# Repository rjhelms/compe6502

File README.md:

# compe6502

A very much work-in-progress homebrew 6502 system.

Hardware is currently built off of a 6502 protoboard, available at https://github.com/rjhelms/6502proto.

All hardware CC-BY-SA 4.0. All software zlib license unless otherwise specified.

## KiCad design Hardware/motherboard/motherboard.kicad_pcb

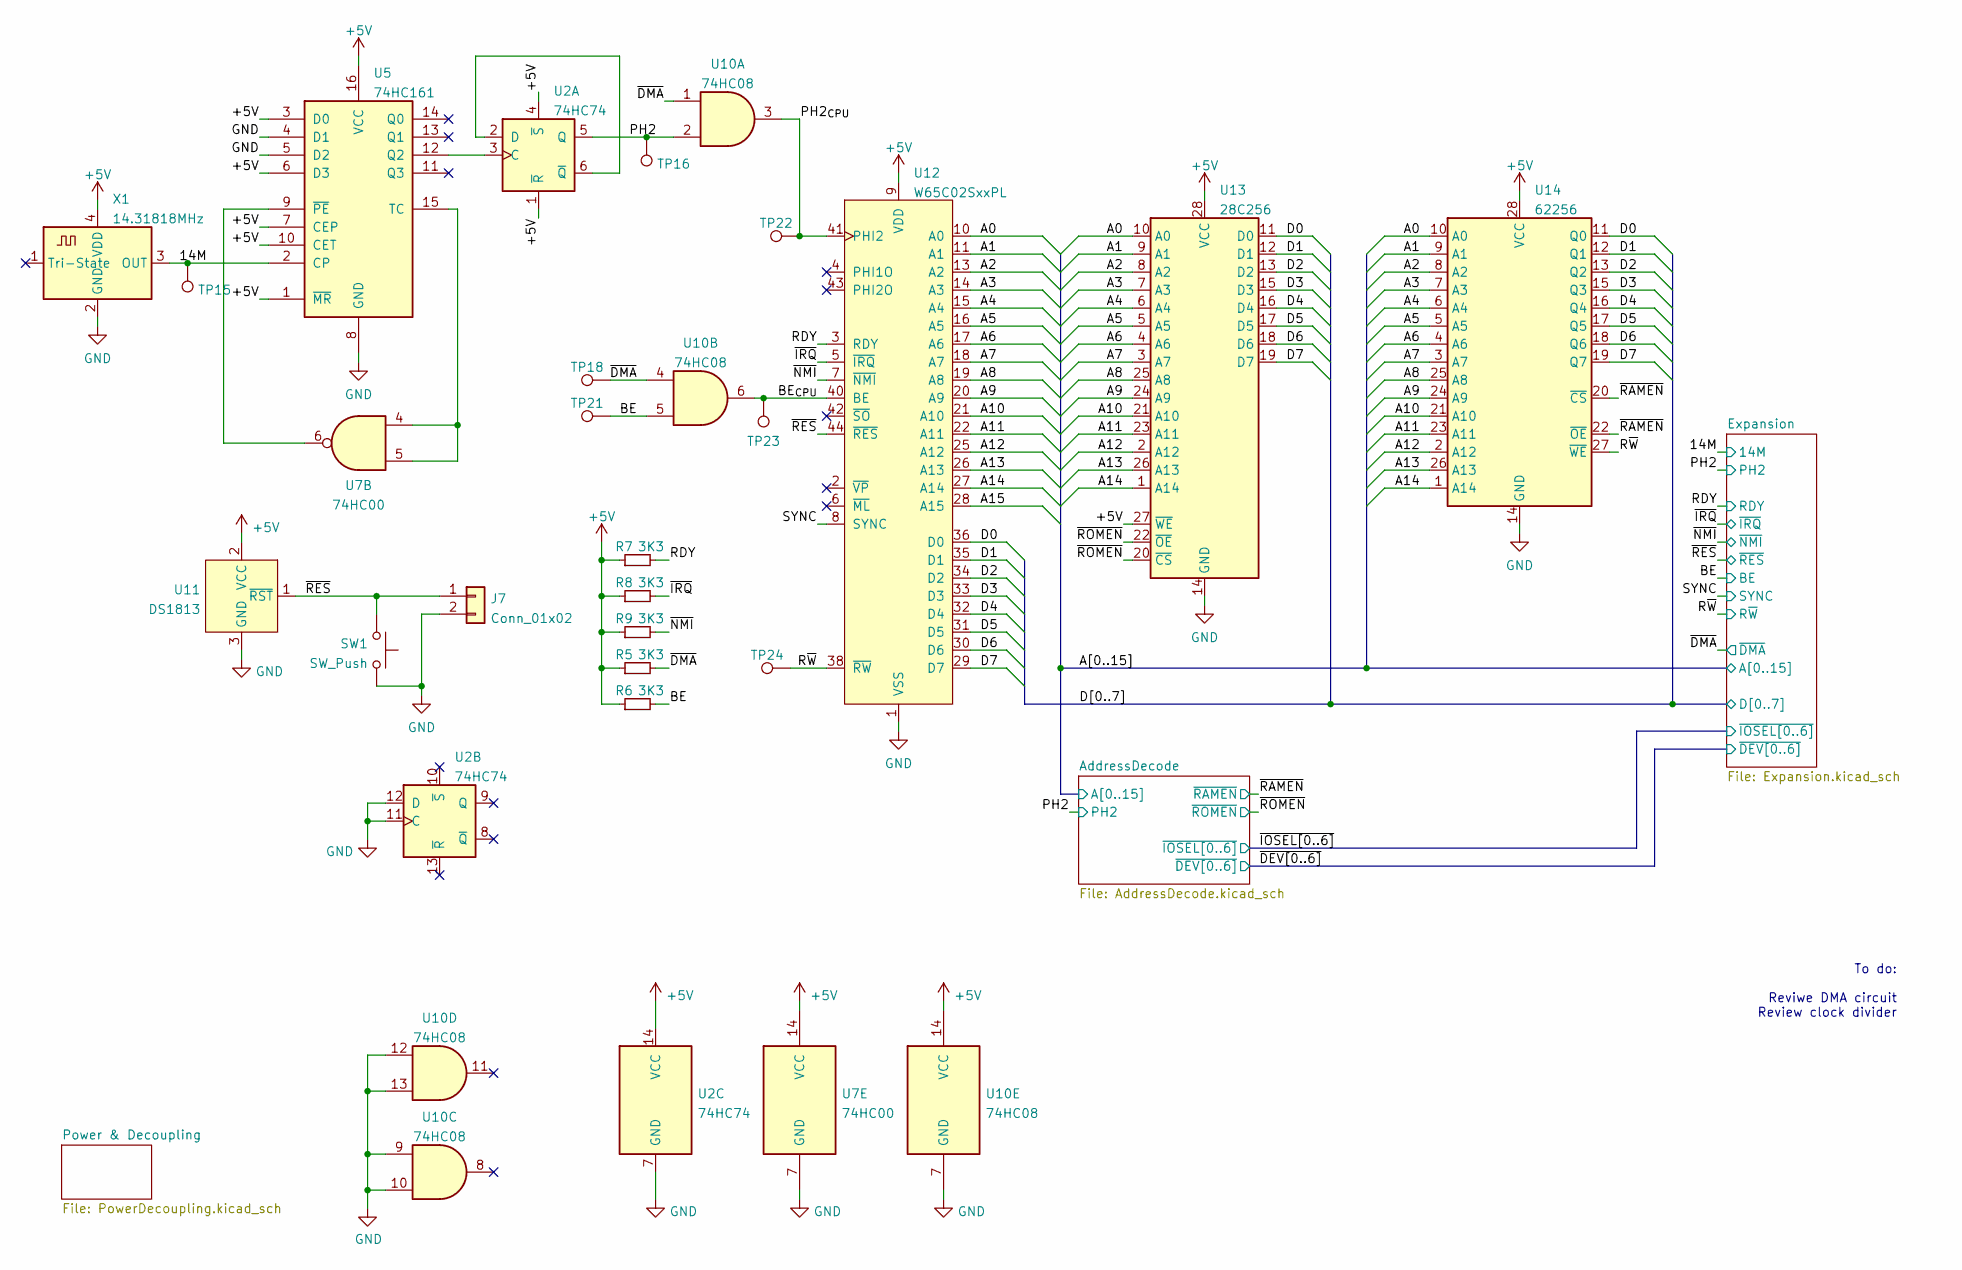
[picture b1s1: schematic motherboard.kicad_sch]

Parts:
J7: Conn_01x02; PinHeader_1x02_P2.54mm_Vertical
R5, R6, R7, R8, R9: 3K3; R_0805_2012Metric
SW1: SW_Push; SW_SPST_B3S-1000
TP15, TP16, TP18, TP21, TP22, TP23, TP24: TestPoint; TestPoint_THTPad_D1.5mm_Drill0.7mm
U2: 74HC74; SOIC-14_3.9x8.7mm_P1.27mm
U5: 74HC161; SOIC-16_3.9x9.9mm_P1.27mm
U7: 74HC00; SOIC-14_3.9x8.7mm_P1.27mm
U10: 74HC08; SOIC-14_3.9x8.7mm_P1.27mm
U11: DS1813; TO-92_Inline
U12: W65C02SxxPL; PLCC-44_THT-Socket
U13: 28C256; DIP-28_W15.24mm_Socket_LongPads
U14: 62256; SOIC-28W_7.5x18.7mm_P1.27mm
X1: 14.31818MHz; Oscillator_SMD_IQD_IQXO70-4Pin_7.5x5.0mm

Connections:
+5V: R5.1, R6.1, R7.1, R8.1, R9.1, U2.1 (~R), U2.4 (~S), U2.14 (VCC), U5.1 (~MR), U5.3 (D0), U5.6 (D3), U5.7 (CEP), U5.10 (CET), U5.16 (VCC), U7.14 (VCC), U10.14 (VCC), U11.2 (VCC), U12.9 (VDD), U12.37 (VDD), U13.27 (~WE), U13.28 (VCC), U14.28 (VCC), X1.4 (VDD); also elsewhere on the board
/14M: TP15.1, U5.2 (CP), X1.3 (OUT); also elsewhere on the board
/A0: U12.10 (A0), U13.10 (A0), U14.10 (A0); also elsewhere on the board
/A1: U12.11 (A1), U13.9 (A1), U14.9 (A1); also elsewhere on the board
/A2: U12.13 (A2), U13.8 (A2), U14.8 (A2); also elsewhere on the board
/A3: U12.14 (A3), U13.7 (A3), U14.7 (A3); also elsewhere on the board
/A4: U12.15 (A4), U13.6 (A4), U14.6 (A4); also elsewhere on the board
/A5: U12.16 (A5), U13.5 (A5), U14.5 (A5); also elsewhere on the board
/A6: U12.17 (A6), U13.4 (A6), U14.4 (A6); also elsewhere on the board
/A7: U12.18 (A7), U13.3 (A7), U14.3 (A7); also elsewhere on the board
/A8: U12.19 (A8), U13.25 (A8), U14.25 (A8); also elsewhere on the board
/A9: U12.20 (A9), U13.24 (A9), U14.24 (A9); also elsewhere on the board
/A10: U12.21 (A10), U13.21 (A10), U14.21 (A10); also elsewhere on the board
/A11: U12.22 (A11), U13.23 (A11), U14.23 (A11); also elsewhere on the board
/A12: U12.25 (A12), U13.2 (A12), U14.2 (A12); also elsewhere on the board
/A13: U12.26 (A13), U13.26 (A13), U14.26 (A13); also elsewhere on the board
/A14: U12.27 (A14), U13.1 (A14), U14.1 (A14); also elsewhere on the board
/A15: U12.28 (A15); also elsewhere on the board
/BE: R6.2, TP21.1, U10.5; also elsewhere on the board
/BE_{CPU}: TP23.1, U10.6, U12.40 (BE)
/D0: U12.36 (D0), U13.11 (D0), U14.11 (Q0); also elsewhere on the board
/D1: U12.35 (D1), U13.12 (D1), U14.12 (Q1); also elsewhere on the board
/D2: U12.34 (D2), U13.13 (D2), U14.13 (Q2); also elsewhere on the board
/D3: U12.33 (D3), U13.15 (D3), U14.15 (Q3); also elsewhere on the board
/D4: U12.32 (D4), U13.16 (D4), U14.16 (Q4); also elsewhere on the board
/D5: U12.31 (D5), U13.17 (D5), U14.17 (Q5); also elsewhere on the board
/D6: U12.30 (D6), U13.18 (D6), U14.18 (Q6); also elsewhere on the board
/D7: U12.29 (D7), U13.19 (D7), U14.19 (Q7); also elsewhere on the board
/PH2: TP16.1, U2.5 (Q), U10.2; also elsewhere on the board
/PH2_{CPU}: TP22.1, U10.3, U12.41 (PHI2)
/RDY: R7.2, U12.3 (RDY); also elsewhere on the board
/R~W: TP24.1, U12.38 (~RW), U14.27 (~WE); also elsewhere on the board
/SYNC: U12.8 (SYNC); also elsewhere on the board
/~DMA: R5.2, TP18.1, U10.1, U10.4; also elsewhere on the board
/~IRQ: R8.2, U12.5 (~IRQ); also elsewhere on the board
/~NMI: R9.2, U12.7 (~NMI); also elsewhere on the board
/~RAMEN: U14.20 (~CS), U14.22 (~OE); also elsewhere on the board
/~RES: J7.1, SW1.1, U11.1 (~RST), U12.44 (~RES); also elsewhere on the board
/~ROMEN: U13.20 (~CS), U13.22 (~OE); also elsewhere on the board
GND: J7.2, SW1.2, U2.7 (GND), U2.11 (C), U2.12 (D), U5.4 (D1), U5.5 (D2), U5.8 (GND), U7.7 (GND), U10.7 (GND), U10.9, U10.10, U10.12, U10.13, U11.3 (GND), U12.1 (VSS), U12.23 (VSS), U12.24 (VSS), U13.14 (GND), U14.14 (GND), X1.2 (GND); also elsewhere on the board
unnamed: U2.2 (D), U2.6 (~Q)
unnamed: U2.3 (C), U5.12 (Q2)
unnamed: U5.9 (~PE), U7.6
unnamed: U5.15 (TC), U7.4, U7.5

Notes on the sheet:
To do: Reviwe DMA circuit Review clock divider

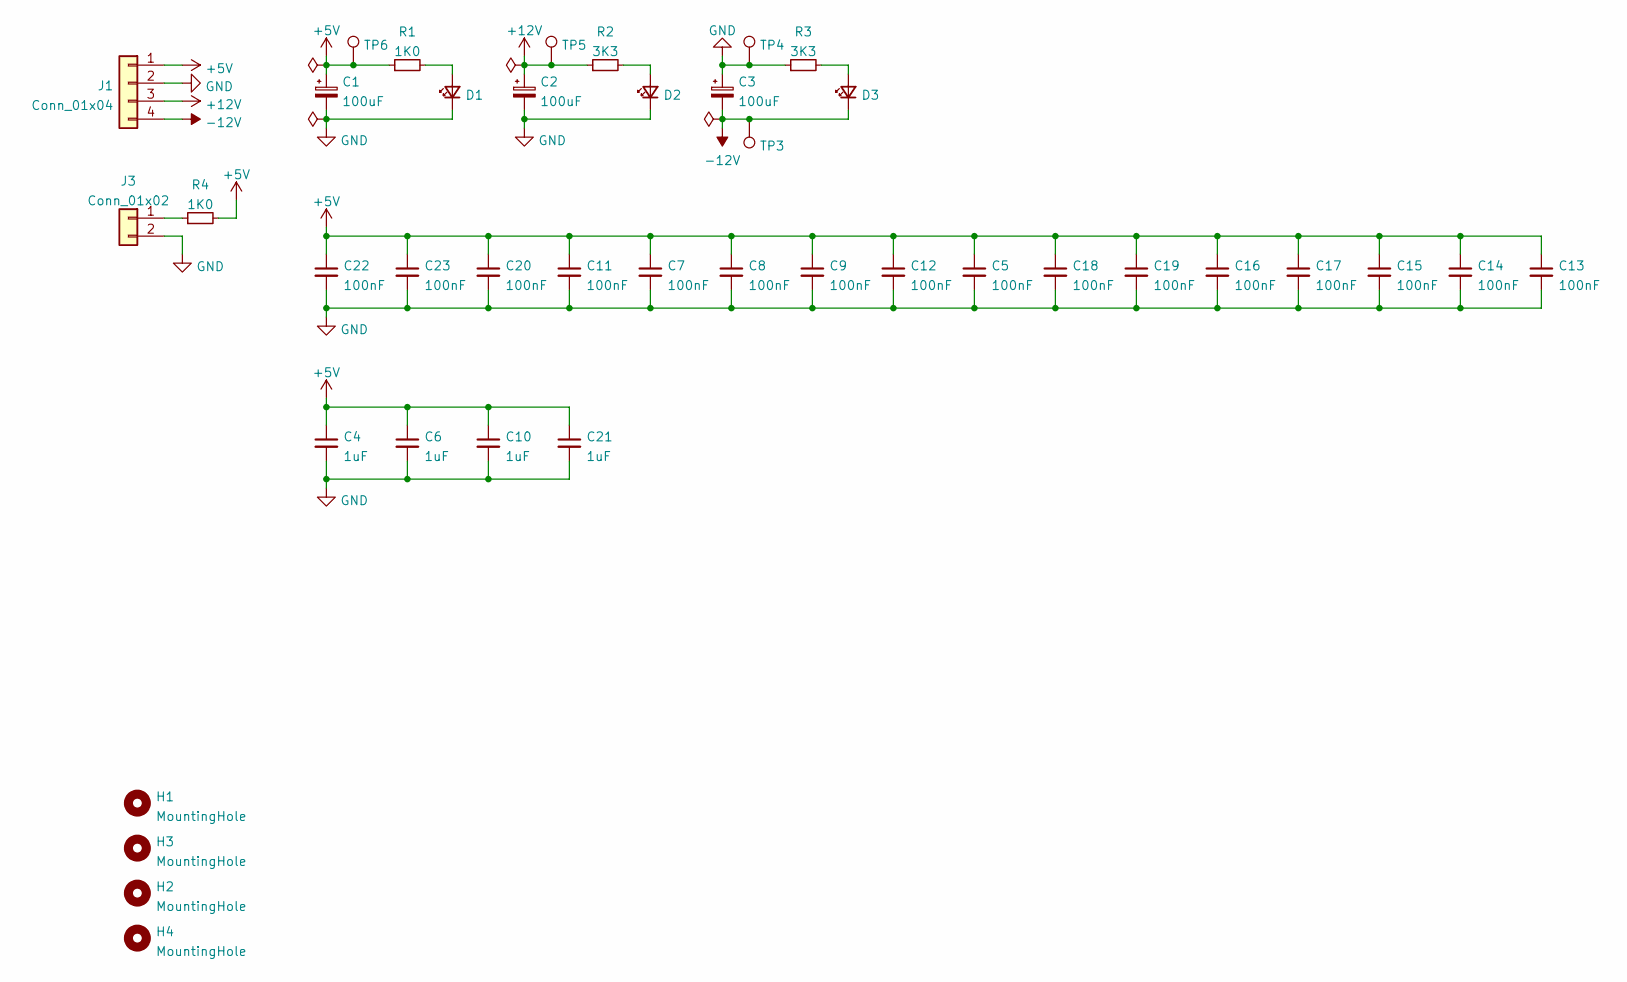
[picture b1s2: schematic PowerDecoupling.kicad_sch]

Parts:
C1, C2, C3: 100uF; CP_Elec_6.3x7.7
C4, C6, C10, C21: 1uF; C_0805_2012Metric
C5, C7, C8, C9, C11, C12, C13, C14, C15, C16, C17, C18, C19, C20, C22, C23: 100nF; C_0805_2012Metric
D1, D2, D3: LED; LED_0805_2012Metric
H1, H2, H3, H4: MountingHole; MountingHole_3.2mm_M3
J1: Conn_01x04; Molex_Micro-Fit_3.0_43045-0400_2x02_P3.00mm_Horizontal
J3: Conn_01x02; PinHeader_1x02_P2.54mm_Vertical
R1, R4: 1K0; R_0805_2012Metric
R2, R3: 3K3; R_0805_2012Metric
TP3, TP4, TP5, TP6: TestPoint; TestPoint_THTPad_D1.5mm_Drill0.7mm

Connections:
+5V: C1.1, C4.1, C5.1, C6.1, C7.1, C8.1, C9.1, C10.1, C11.1, C12.1, C13.1, C14.1, C15.1, C16.1, C17.1, C18.1, C19.1, C20.1, C21.1, C22.1, C23.1, J1.1, R1.1, R4.2, TP6.1; also elsewhere on the board
+12V: C2.1, J1.3, R2.1, TP5.1; also elsewhere on the board
-12V: C3.2, D3.1 (K), J1.4, TP3.1; also elsewhere on the board
GND: C1.2, C2.2, C3.1, C4.2, C5.2, C6.2, C7.2, C8.2, C9.2, C10.2, C11.2, C12.2, C13.2, C14.2, C15.2, C16.2, C17.2, C18.2, C19.2, C20.2, C21.2, C22.2, C23.2, D1.1 (K), D2.1 (K), J1.2, J3.2, R3.1, TP4.1; also elsewhere on the board
unnamed: D1.2 (A), R1.2
unnamed: D2.2 (A), R2.2
unnamed: D3.2 (A), R3.2
unnamed: J3.1, R4.1

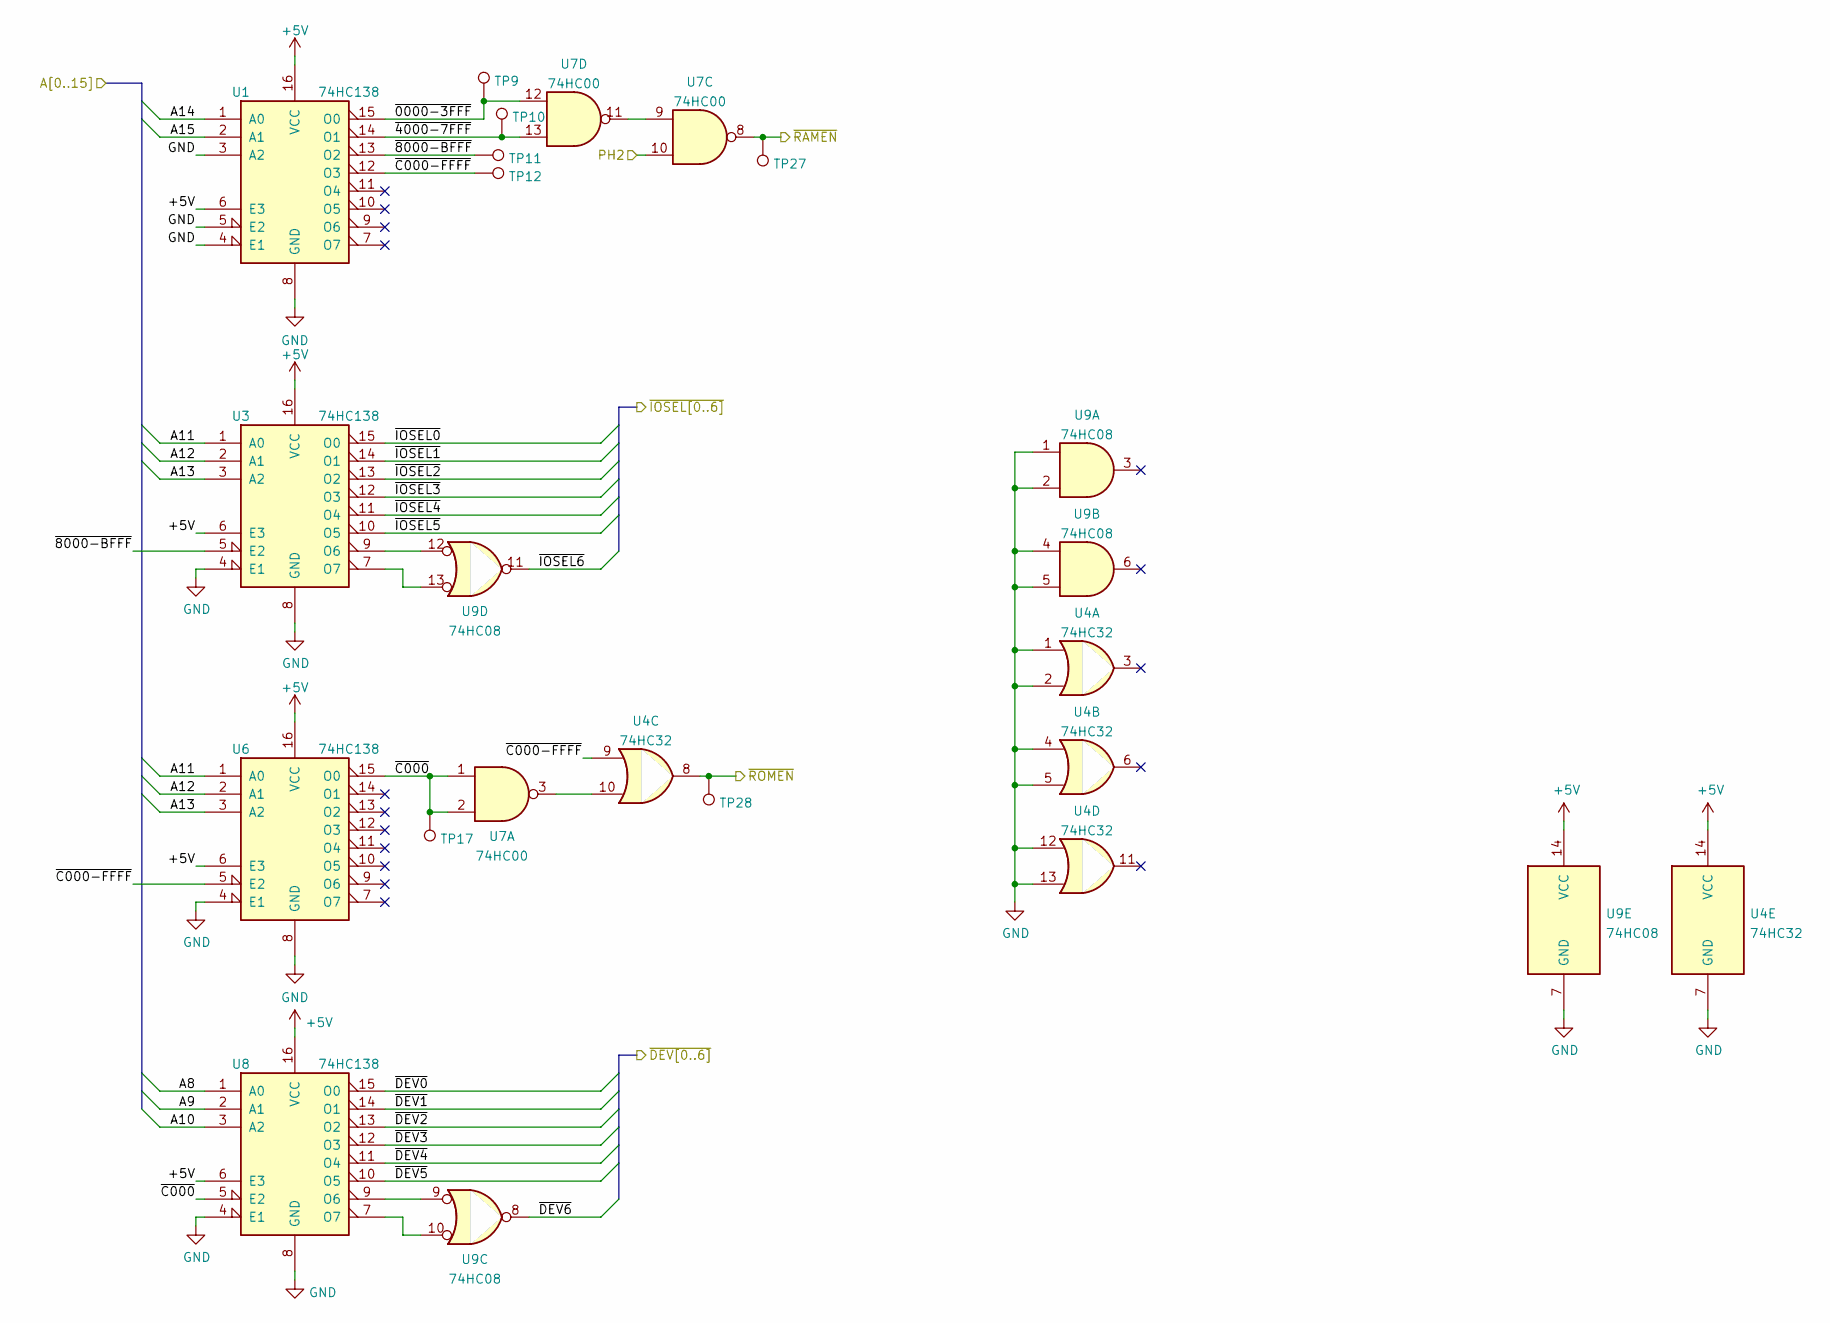
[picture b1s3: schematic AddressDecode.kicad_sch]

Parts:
TP9, TP10, TP11, TP12, TP17, TP27, TP28: TestPoint; TestPoint_THTPad_D1.5mm_Drill0.7mm
U1, U3, U6, U8: 74HC138; SOIC-16_3.9x9.9mm_P1.27mm; MPN SN74HC138N
U4: 74HC32; SOIC-14_3.9x8.7mm_P1.27mm
U7: 74HC00; SOIC-14_3.9x8.7mm_P1.27mm
U9: 74HC08; SOIC-14_3.9x8.7mm_P1.27mm

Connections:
+5V: U1.6 (E3), U1.16 (VCC), U3.6 (E3), U3.16 (VCC), U4.14 (VCC), U6.6 (E3), U6.16 (VCC), U8.6 (E3), U8.16 (VCC), U9.14 (VCC); also elsewhere on the board
/A8: U8.1 (A0); also elsewhere on the board
/A9: U8.2 (A1); also elsewhere on the board
/A10: U8.3 (A2); also elsewhere on the board
/A11: U3.1 (A0), U6.1 (A0); also elsewhere on the board
/A12: U3.2 (A1), U6.2 (A1); also elsewhere on the board
/A13: U3.3 (A2), U6.3 (A2); also elsewhere on the board
/A14: U1.1 (A0); also elsewhere on the board
/A15: U1.2 (A1); also elsewhere on the board
/AddressDecode/~0000-3FFF: TP9.1, U1.15 (O0), U7.12
/AddressDecode/~4000-7FFF: TP10.1, U1.14 (O1), U7.13
/AddressDecode/~8000-BFFF: TP11.1, U1.13 (O2), U3.5 (E2)
/AddressDecode/~C000-FFFF: TP12.1, U1.12 (O3), U4.9, U6.5 (E2)
/AddressDecode/~C000: TP17.1, U6.15 (O0), U7.1, U7.2, U8.5 (E2)
/PH2: U7.10; also elsewhere on the board
/~DEV0: U8.15 (O0); also elsewhere on the board
/~DEV1: U8.14 (O1); also elsewhere on the board
/~DEV2: U8.13 (O2); also elsewhere on the board
/~DEV3: U8.12 (O3); also elsewhere on the board
/~DEV4: U8.11 (O4); also elsewhere on the board
/~DEV5: U8.10 (O5); also elsewhere on the board
/~DEV6: U9.8; also elsewhere on the board
/~IOSEL0: U3.15 (O0); also elsewhere on the board
/~IOSEL1: U3.14 (O1); also elsewhere on the board
/~IOSEL2: U3.13 (O2); also elsewhere on the board
/~IOSEL3: U3.12 (O3); also elsewhere on the board
/~IOSEL4: U3.11 (O4); also elsewhere on the board
/~IOSEL5: U3.10 (O5); also elsewhere on the board
/~IOSEL6: U9.11; also elsewhere on the board
/~RAMEN: TP27.1, U7.8; also elsewhere on the board
/~ROMEN: TP28.1, U4.8; also elsewhere on the board
GND: U1.3 (A2), U1.4 (E1), U1.5 (E2), U1.8 (GND), U3.4 (E1), U3.8 (GND), U4.1, U4.2, U4.4, U4.5, U4.7 (GND), U4.12, U4.13, U6.4 (E1), U6.8 (GND), U8.4 (E1), U8.8 (GND), U9.1, U9.2, U9.4, U9.5, U9.7 (GND); also elsewhere on the board
unnamed: U3.7 (O7), U9.13
unnamed: U3.9 (O6), U9.12
unnamed: U4.10, U7.3
unnamed: U7.9, U7.11
unnamed: U8.7 (O7), U9.10
unnamed: U8.9 (O6), U9.9

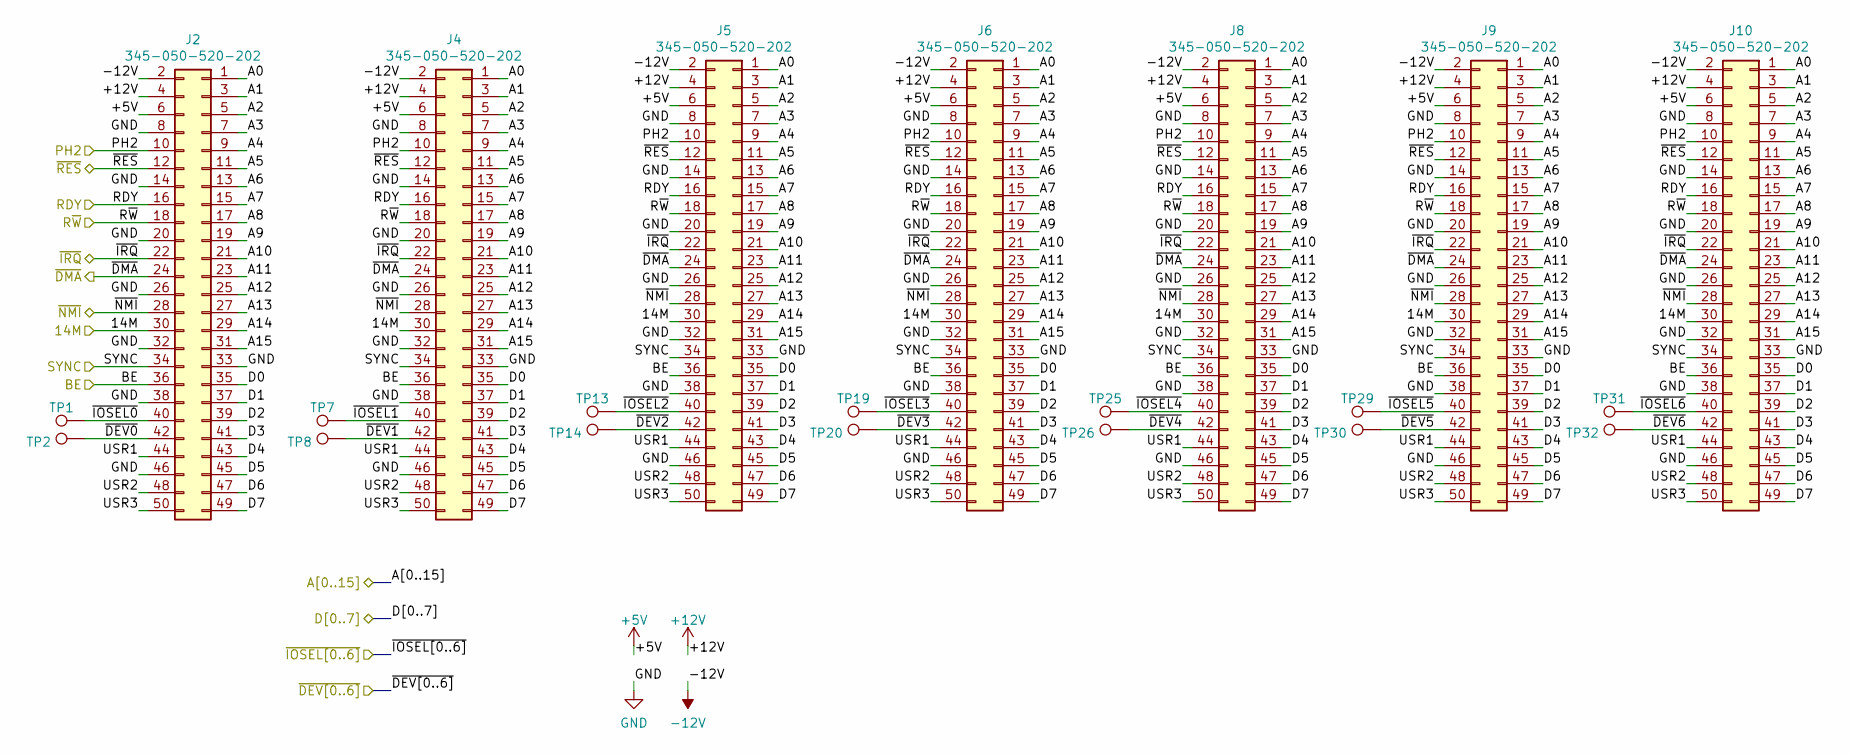
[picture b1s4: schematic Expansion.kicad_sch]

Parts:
J2, J4, J5, J6, J8, J9, J10: 345-050-520-202; EDAC_345-050-520-202; MPN 345-050-520-202
TP1, TP2, TP7, TP8, TP13, TP14, TP19, TP20, TP25, TP26, TP29, TP30, TP31, TP32: TestPoint; TestPoint_THTPad_D1.5mm_Drill0.7mm

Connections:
+5V: J2.6, J4.6, J5.6, J6.6, J8.6, J9.6, J10.6; also elsewhere on the board
+12V: J2.4, J4.4, J5.4, J6.4, J8.4, J9.4, J10.4; also elsewhere on the board
-12V: J2.2, J4.2, J5.2, J6.2, J8.2, J9.2, J10.2; also elsewhere on the board
/14M: J2.30, J4.30, J5.30, J6.30, J8.30, J9.30, J10.30; also elsewhere on the board
/A0: J2.1, J4.1, J5.1, J6.1, J8.1, J9.1, J10.1; also elsewhere on the board
/A1: J2.3, J4.3, J5.3, J6.3, J8.3, J9.3, J10.3; also elsewhere on the board
/A2: J2.5, J4.5, J5.5, J6.5, J8.5, J9.5, J10.5; also elsewhere on the board
/A3: J2.7, J4.7, J5.7, J6.7, J8.7, J9.7, J10.7; also elsewhere on the board
/A4: J2.9, J4.9, J5.9, J6.9, J8.9, J9.9, J10.9; also elsewhere on the board
/A5: J2.11, J4.11, J5.11, J6.11, J8.11, J9.11, J10.11; also elsewhere on the board
/A6: J2.13, J4.13, J5.13, J6.13, J8.13, J9.13, J10.13; also elsewhere on the board
/A7: J2.15, J4.15, J5.15, J6.15, J8.15, J9.15, J10.15; also elsewhere on the board
/A8: J2.17, J4.17, J5.17, J6.17, J8.17, J9.17, J10.17; also elsewhere on the board
/A9: J2.19, J4.19, J5.19, J6.19, J8.19, J9.19, J10.19; also elsewhere on the board
/A10: J2.21, J4.21, J5.21, J6.21, J8.21, J9.21, J10.21; also elsewhere on the board
/A11: J2.23, J4.23, J5.23, J6.23, J8.23, J9.23, J10.23; also elsewhere on the board
/A12: J2.25, J4.25, J5.25, J6.25, J8.25, J9.25, J10.25; also elsewhere on the board
/A13: J2.27, J4.27, J5.27, J6.27, J8.27, J9.27, J10.27; also elsewhere on the board
/A14: J2.29, J4.29, J5.29, J6.29, J8.29, J9.29, J10.29; also elsewhere on the board
/A15: J2.31, J4.31, J5.31, J6.31, J8.31, J9.31, J10.31; also elsewhere on the board
/BE: J2.36, J4.36, J5.36, J6.36, J8.36, J9.36, J10.36; also elsewhere on the board
/D0: J2.35, J4.35, J5.35, J6.35, J8.35, J9.35, J10.35; also elsewhere on the board
/D1: J2.37, J4.37, J5.37, J6.37, J8.37, J9.37, J10.37; also elsewhere on the board
/D2: J2.39, J4.39, J5.39, J6.39, J8.39, J9.39, J10.39; also elsewhere on the board
/D3: J2.41, J4.41, J5.41, J6.41, J8.41, J9.41, J10.41; also elsewhere on the board
/D4: J2.43, J4.43, J5.43, J6.43, J8.43, J9.43, J10.43; also elsewhere on the board
/D5: J2.45, J4.45, J5.45, J6.45, J8.45, J9.45, J10.45; also elsewhere on the board
/D6: J2.47, J4.47, J5.47, J6.47, J8.47, J9.47, J10.47; also elsewhere on the board
/D7: J2.49, J4.49, J5.49, J6.49, J8.49, J9.49, J10.49; also elsewhere on the board
/Expansion/USR1: J2.44, J4.44, J5.44, J6.44, J8.44, J9.44, J10.44
/Expansion/USR2: J2.48, J4.48, J5.48, J6.48, J8.48, J9.48, J10.48
/Expansion/USR3: J2.50, J4.50, J5.50, J6.50, J8.50, J9.50, J10.50
/PH2: J2.10, J4.10, J5.10, J6.10, J8.10, J9.10, J10.10; also elsewhere on the board
/RDY: J2.16, J4.16, J5.16, J6.16, J8.16, J9.16, J10.16; also elsewhere on the board
/R~W: J2.18, J4.18, J5.18, J6.18, J8.18, J9.18, J10.18; also elsewhere on the board
/SYNC: J2.34, J4.34, J5.34, J6.34, J8.34, J9.34, J10.34; also elsewhere on the board
/~DEV0: J2.42, TP2.1; also elsewhere on the board
/~DEV1: J4.42, TP8.1; also elsewhere on the board
/~DEV2: J5.42, TP14.1; also elsewhere on the board
/~DEV3: J6.42, TP20.1; also elsewhere on the board
/~DEV4: J8.42, TP26.1; also elsewhere on the board
/~DEV5: J9.42, TP30.1; also elsewhere on the board
/~DEV6: J10.42, TP32.1; also elsewhere on the board
/~DMA: J2.24, J4.24, J5.24, J6.24, J8.24, J9.24, J10.24; also elsewhere on the board
/~IOSEL0: J2.40, TP1.1; also elsewhere on the board
/~IOSEL1: J4.40, TP7.1; also elsewhere on the board
/~IOSEL2: J5.40, TP13.1; also elsewhere on the board
/~IOSEL3: J6.40, TP19.1; also elsewhere on the board
/~IOSEL4: J8.40, TP25.1; also elsewhere on the board
/~IOSEL5: J9.40, TP29.1; also elsewhere on the board
/~IOSEL6: J10.40, TP31.1; also elsewhere on the board
/~IRQ: J2.22, J4.22, J5.22, J6.22, J8.22, J9.22, J10.22; also elsewhere on the board
/~NMI: J2.28, J4.28, J5.28, J6.28, J8.28, J9.28, J10.28; also elsewhere on the board
/~RES: J2.12, J4.12, J5.12, J6.12, J8.12, J9.12, J10.12; also elsewhere on the board
GND: J2.8, J2.14, J2.20, J2.26, J2.32, J2.33, J2.38, J2.46, J4.8, J4.14, J4.20, J4.26, J4.32, J4.33, J4.38, J4.46, J5.8, J5.14, J5.20, J5.26, J5.32, J5.33, J5.38, J5.46, J6.8, J6.14, J6.20, J6.26, J6.32, J6.33, J6.38, J6.46, J8.8, J8.14, J8.20, J8.26, J8.32, J8.33, J8.38, J8.46, J9.8, J9.14, J9.20, J9.26, J9.32, J9.33, J9.38, J9.46, J10.8, J10.14, J10.20, J10.26, J10.32, J10.33, J10.38, J10.46; also elsewhere on the board

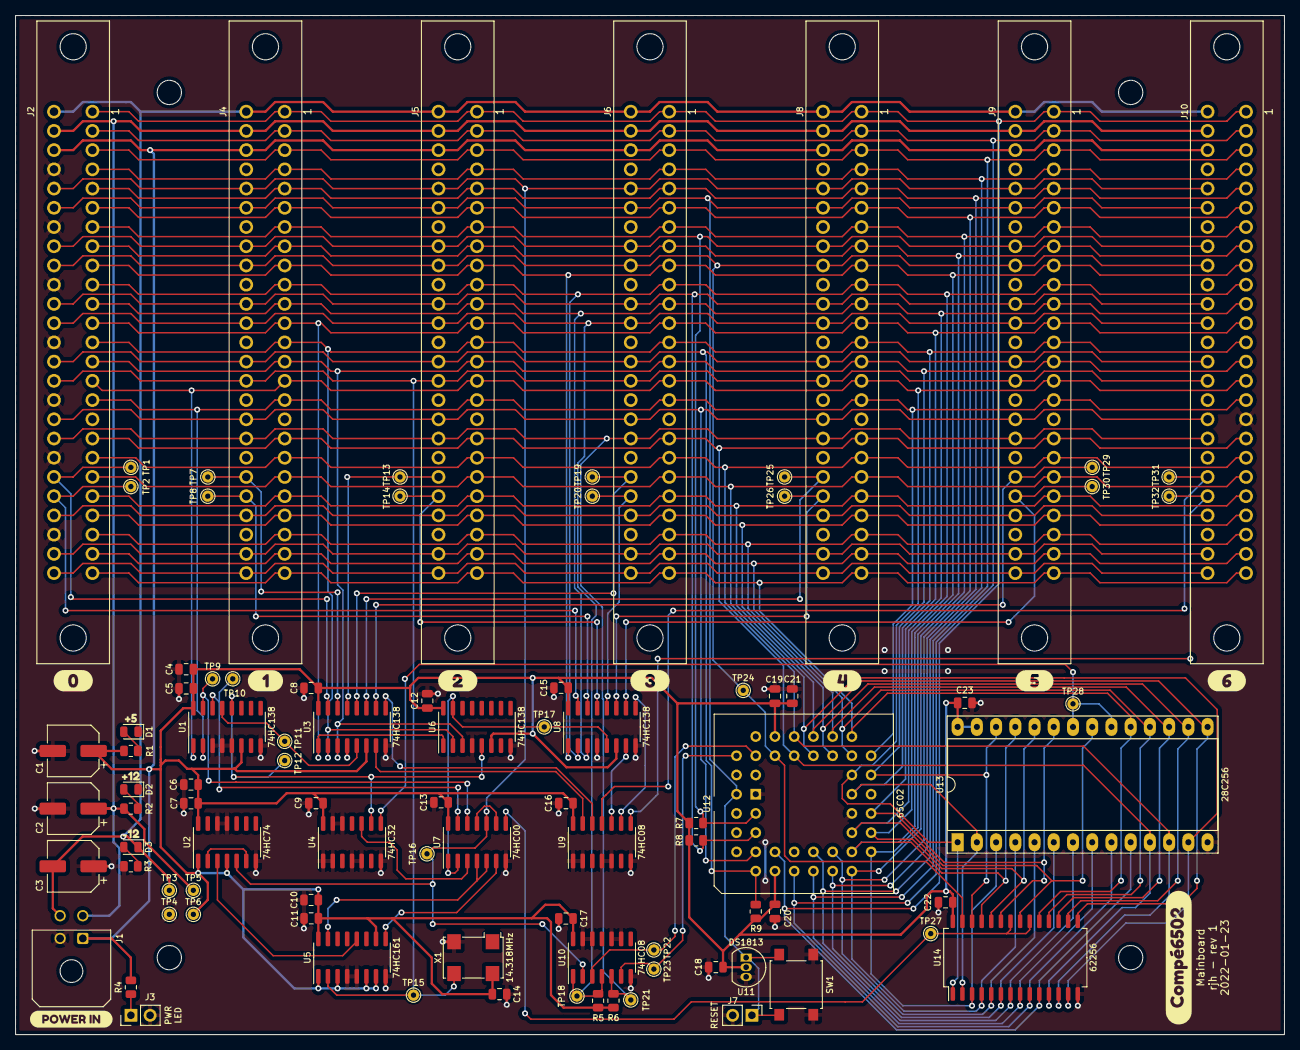
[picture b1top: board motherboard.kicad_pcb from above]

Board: 2 copper layers, 167.6 x 134.6 mm, 110 parts (1 on the bottom side), 78 nets.

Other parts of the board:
kibuzzard-1: G***; kibuzzard-61E47B61
kibuzzard-2: G***; kibuzzard-61E4A308
kibuzzard-3: G***; kibuzzard-61E48162
kibuzzard-4: G***; kibuzzard-61E4816D
kibuzzard-5: G***; kibuzzard-61E48181
kibuzzard-6: G***; kibuzzard-61E47B68
kibuzzard-7: G***; kibuzzard-61E47B6E
kibuzzard-8: G***; kibuzzard-61E47B74
kibuzzard-9: G***; kibuzzard-61E47B79
kibuzzard-10: G***; kibuzzard-61E47B7F
kibuzzard-11, kibuzzard-13: G***; kibuzzard-61E4DE7F
kibuzzard-12: G***; kibuzzard-61E47B85

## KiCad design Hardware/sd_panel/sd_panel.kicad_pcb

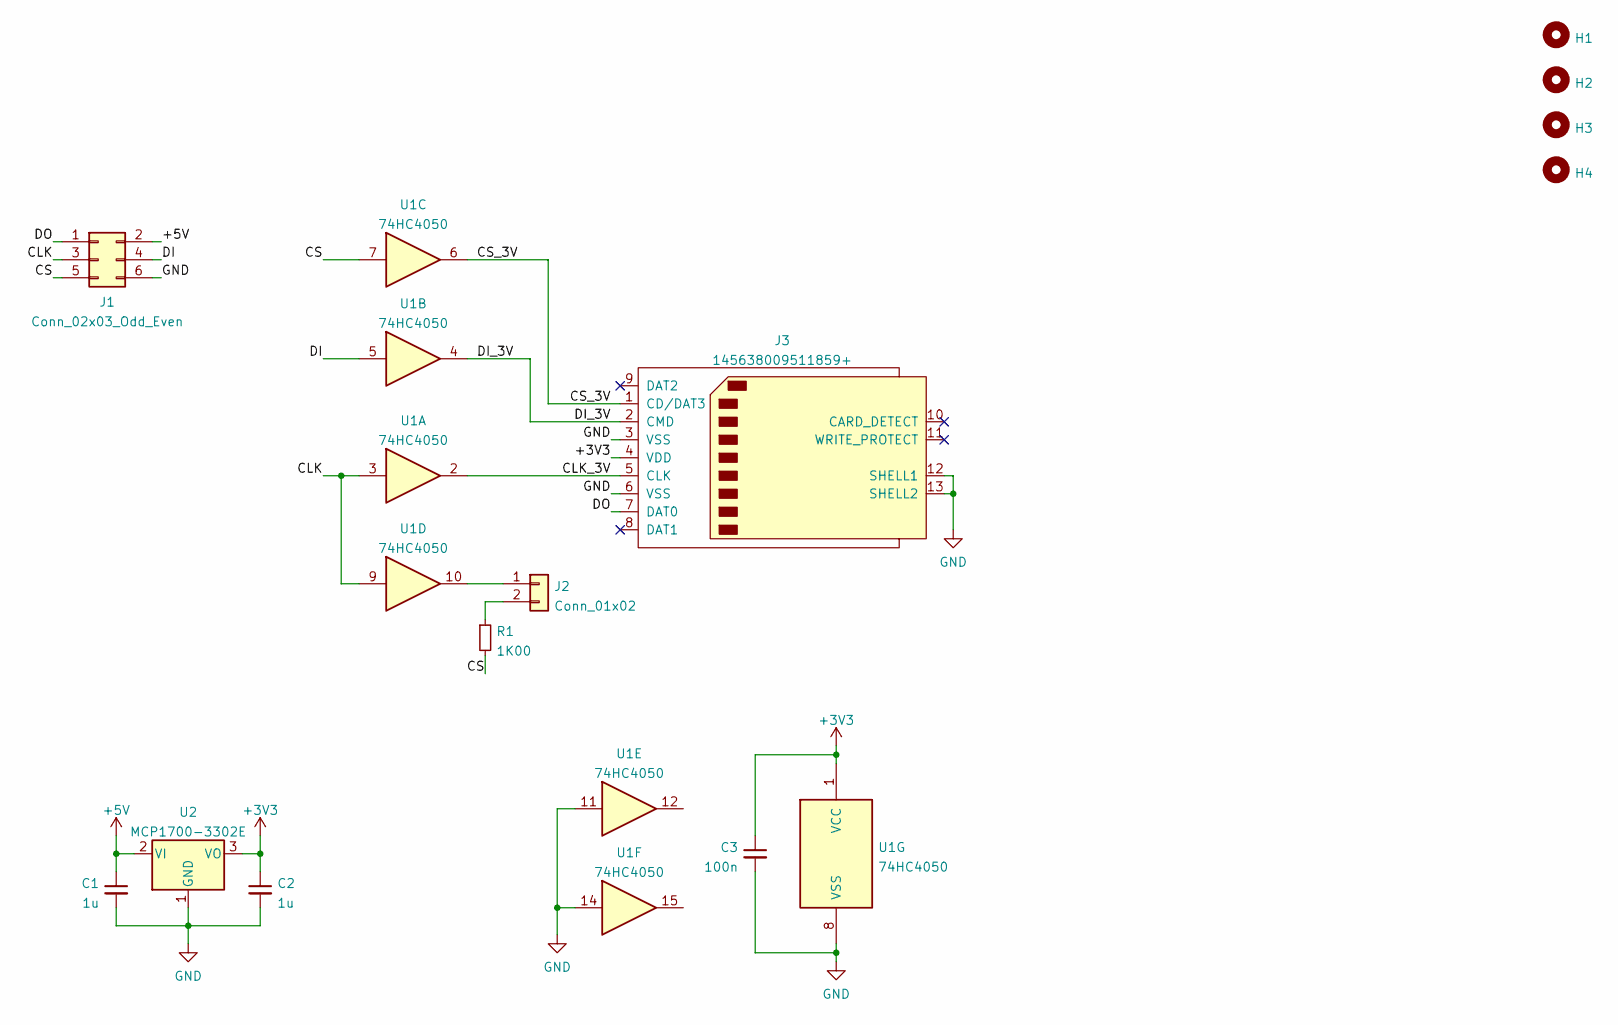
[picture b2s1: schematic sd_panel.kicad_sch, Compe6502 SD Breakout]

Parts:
C1, C2: 1u; C_0805_2012Metric
C3: 100n; C_0805_2012Metric
H1, H2, H3, H4: MountingHole; MountingHole_3.2mm_M3
J1: Conn_02x03_Odd_Even; PinHeader_2x03_P2.54mm_Vertical
J2: Conn_01x02; PinHeader_1x02_P2.54mm_Vertical
J3: 145638009511859+; SD_Kyocera_145638009511859+
R1: 1K00; R_0805_2012Metric
U1: 74HC4050; SOIC-16_3.9x9.9mm_P1.27mm
U2: MCP1700-3302E; SOT-23

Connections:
+3V3: C2.1, C3.1, J3.4 (VDD), U1.1 (VCC), U2.3 (VO)
+5V: C1.1, J1.2, U2.2 (VI)
/CLK: J1.3, U1.3, U1.9
/CLK_3V: J3.5 (CLK), U1.2
/CS: J1.5, R1.2, U1.7
/CS_3V: J3.1 (CD/DAT3), U1.6
/DI: J1.4, U1.5
/DI_3V: J3.2 (CMD), U1.4
/DO: J1.1, J3.7 (DAT0)
GND: C1.2, C2.2, C3.2, J1.6, J3.3 (VSS), J3.6 (VSS), J3.12 (SHELL1), J3.13 (SHELL2), U1.8 (VSS), U1.11, U1.14, U2.1 (GND)
unnamed: J2.2, R1.1
unnamed: J2.1, U1.10

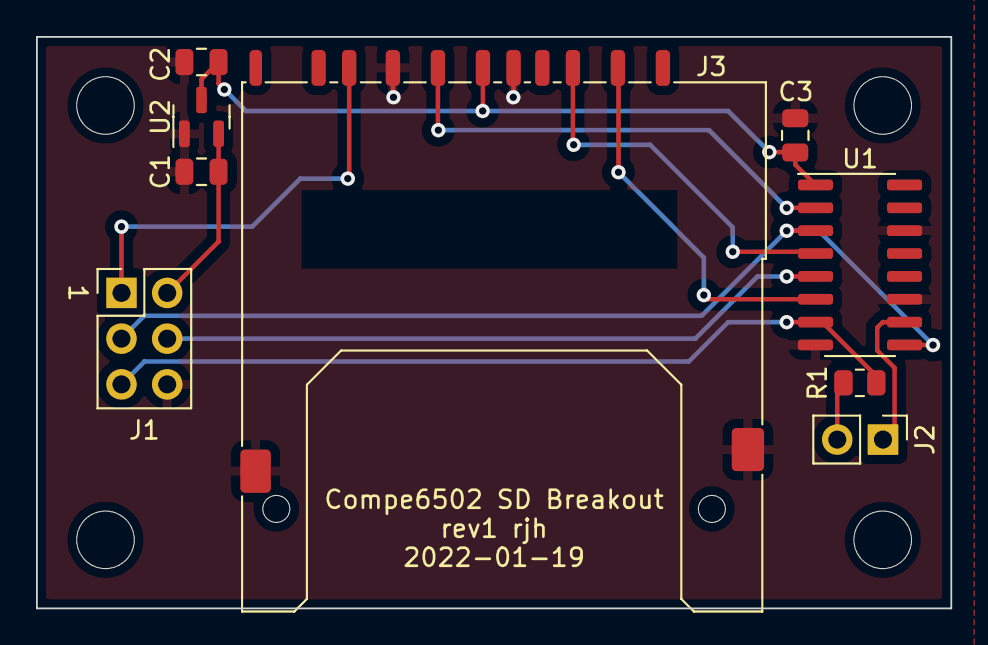
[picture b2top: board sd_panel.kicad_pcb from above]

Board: 2 copper layers, 50.8 x 31.8 mm, 13 parts (0 on the bottom side), 12 nets.

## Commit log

2021-12-24 Add existing ROM
2021-12-24 Tweak LORAM size
    Will need 4 pages:
    - input buffer
    - vector page
    - 2 pages for SD card workspace
2021-12-24 Add SHOWMSG to jump table
2021-12-24 Change license to zlib
    To be more compatible with cc65, when implementing libraries etc
2021-12-24 Add library
    (Most of) conio routines
2021-12-24 Add Hangman example
2021-12-24 Remove temp folder
    Accidentally committed
2021-12-24 Add hardware
2021-12-24 Add Hangman readme
2021-12-24 Move hangman readme to right place
2021-12-24 Lol I'm bad at this
2021-12-24 Remove high-byte shenanigans
    Resolves issue #2
2021-12-24 Revert "Remove high-byte shenanigans"
    This reverts commit 9633a3e1fe7fa055c475b0a9d931e8913273d5e0.
2021-12-24 Add vector tables
2021-12-24 Move status display into MON
    BIOS page was full - so bump MON up to 3 pages and move that method there.
2021-12-24 Fix video clear line
    Resolves #5.
2021-12-24 Update video_ribbons.kicad_pcb
    Also part of fix for #5
2021-12-24 Fix backplane LEDs
    Resolves issue #4
2021-12-24 Change address decode on backplane
    Resolves issue #3
2021-12-24 Increment backplane rev & date
2021-12-24 Add dynamic ROM checksum
    Just for grins
2021-12-24 Improve PRSTATUS display
    Make BRK output easier to parse
2021-12-27 Ewoz: bypass high-bit logic
    Use COUT instead of ECHO in SHWMSG, to bypass high-bit logic.
    Should resolve #2.
2021-12-31 Prep rom for I/O card
    Use handshake rather than pulse mode for keyboard reads, so keyboard MCU won't have to rely on interrupt
2022-01-03 Add cassette routines to ROM
2022-01-05 Add cassette load to ROM
    Also, utility for converting bin files to waves
2022-01-05 Add checksum every 256 bytes to cassette format
    Doesn't make it more reliable, but makes it fail faster
2022-01-07 Move startup message out of ewoz
    Want to see it when coldbooting into basic
    This means there is no difference between M_COLDRESET and M_WARMRESET.
2022-01-07 Fix DC offset in bin2tape
2022-01-08 Add cassette save routine
2022-01-09 Add notes for BASIC implementation
2022-01-09 Assemble ROM sources to separate objects
2022-01-09 Create SYS segment
2022-01-09 Change VECT_TAB and SD_WORK segs to type BSS
    Otherwise these show up as offsets in the output file for some reason
2022-01-09 Update EWOZ "license"
2022-01-10 Clean up ROM build
2022-01-10 Add MSBASIC to repo
2022-01-10 Update makefile and config to get ready for BASIC
2022-01-10 Use ZPBASIC for zeropage.s
2022-01-10 Minimum viable BASIC implementation
2022-01-10 Add in KBD GET_UPPER patch
    Part of #16 - this casts tokens the upper case.
    Lower-case variable names throw a syntax error, maybe there is a similar change needed elsewhere.
2022-01-10 Add HOME command
    Resolves #17.
2022-01-12 Partial implementation of BASIC load & save
    Work towards #14. Not capturing / saving a file name yet.
2022-01-16 Work on motherboard design
2022-01-17 Complete mobo first draft
2022-02-02 Misc hardware work
2022-02-02 Hook in KBD check for CHRGET
    Not perfect, but addresses more of #16
2022-02-02 Add asterisk as monitor prompt
    Resolves #15
2022-08-04 Begin ROM support for PicoVGA routines
2022-08-04 Add MS line editing support
    This adds some QoL towards #13
2022-08-04 Update gitignore
2022-08-06 Replace CR with LF for PicoVGA
2022-08-07 More CR to LF changes
    Missed a few in EWOZ
2022-08-07 Even more CR to LF
    In cassette routines
2022-08-07 Even more CR-to-LF changes
    Again in EWOZ. I think this might be it?
2022-08-07 Lol nope
2022-08-07 Add bin2byte utility
    For converting binary data into cc65 .byte directives
2022-08-08 Add PicoVGA SDK & project
    Not sure how/if this needs to be in here, lol
2022-08-08 Add bin2tape_raw
2022-08-08 Add picovga interface doc
    Work in progress!
2022-08-15 Add cursor rendering
    Work towards #20, currently always on.
2022-08-16 Add absolute cursor moves
2022-08-16 Add cursor enable/disable
2022-08-16 Add cursor locate commands
    First time getting sending data from Pico
2022-08-16 Port conio to Pico board
    Amazed that worked this well
2022-08-16 Improvements to hangmang
    Remove uses to cprintf to save 1.5kb, and show cursor
2022-08-16 Add color commands in prep for conio color
2022-08-16 Misc pico-side tweaks
2022-08-16 Add conio color routines
2022-08-16 Add color to hangman
2022-08-16 VScode forced include for __fastcall__
    For proper parsing of header files
2022-08-16 Move video to slot 7
    That's where it belongs!
2022-08-16 Add picoVGA firmware (#26)
    * Begin ROM support for PicoVGA routines
    * Replace CR with LF for PicoVGA
    * More CR to LF changes
    Missed a few in EWOZ
    * Even more CR to LF
    In cassette routines
2022-08-16 Add warm reset vector
    For issue #22
2022-08-17 TGI support & 1bpp driver
2022-08-18 Add partial 4bpp driver
    Dynamic palette support still to-do
2022-08-19 Add VIA timer to ROM
2022-08-20 Add _clock to assembly lib
    Or could this just be a pointer reference?
2022-08-20 Reinitialize timer on warm reset
    VIA loses all its state
2022-08-20 Fix: dsable cursor at end of cgetc
2022-08-20 Fix: toggle cursor on TextAdvanceWrap
    Man the way conio does this is weird.
2022-08-20 Add text-mode clock example
    Will redo this in TGI after merge
2022-08-20 Change to 64 ticks per second
    This divides evenly into a 1MHz clock freq - so better for now.
2022-08-20 Update example clock program
    - 80-col text for better resolution
    - use CLOCK_PER_SEC rather than hardcoded 60
    - draw full lock hands
2022-08-21 Port example/clock to TGI
2022-08-23 Free running clock render
    In prep for double buffering
2022-08-23 Update picovga interface doc
2022-08-23 Increase cassette interface speed to 600bps
2022-08-23 Correct comments in CWAIT
2022-08-24 Add second graphics page
2022-08-24 Update interface doc
2022-08-24 Add 8bpp driver
2022-08-24 Add compile-time driver selection to clock.c
2022-08-28 Fix 4bpp color mapping
2022-08-28 Runtime color selection for clock
2022-08-28 Clock makefile & readme
2022-08-28 Update color defines
2022-08-28 Remove surplus ROM function
    Not sure when this happened but BIOS segment was overflowing, so removed some dead code
2022-08-28 Update cassette speed to 1200bps, only somewhat working
2022-08-28 Add dynamic speed control
    Cycles for CWAIT are specified in tape header, which is always recorded at 600bps. CSAVE routine is fixed to work at 600bps, CLOAD reads from tape.
2022-08-28 Fix welcome text
    Was using old character set. Also add colour just for fun
2022-08-29 Optimizations to example programs
    Mostly static locals
2022-09-03 Add sd work to date
2022-09-03 Further SD optimization
    Reads only full 512-byte blocks, store results to 0x0400
2022-09-03 Fix blit command
    Caught while doing image demo
2022-09-03 Remove unneeded local var in pf_mount
2022-09-03 pf_read optimizations
    Pull bytes read into a static var, and remove some checks never needed for 512-byte reads
2022-09-03 Reinstate check deleted in error
    Don't need to check btr in a loop, but do need to check it for EOF.
2022-09-03 Replace ld_word and ld_dword with macros
    On a little-endian system, these functions were just expensive pointer casts
2022-09-03 Convert tabs to spaces
    Don't @ me
2022-09-03 Explicity move all mmcbpp vars to global scope
    More straightforward for conversion to assembly
2022-09-03 Replace _dly_us with assembly function
2022-09-03 Port skip_mmc to assembly function
2022-09-03 Port init_port & xmit_mmc to assembly
2022-09-03 Port release_spi & rcvr_mmc to assembly
2022-09-04 Port send_cmd to assembly
    All the internal functions of mmcbpp are ported!
2022-09-04 Port disk_initialize to assembly
2022-09-04 Port disk_readp to assembly
    There's nothing left in mmcbbp.c - can probably delete it
2022-09-05 Remove mmcbbp.c/.h, no longer used
2022-09-05 Clean up mmcasm exports & BSS
2022-09-05 Rename mmcbbp.s
    To match original C name
2022-09-05 Remove locals from pf_read
2022-09-05 Remove locals from pf_open
2022-09-05 Remove locals from dir_find and follow_path
2022-09-05 Remove locals from pf_mount
2022-09-05 Remove follow_path
    Put path directly into dj.fn instead. This means that only files in the root directory can be loaded.
2022-09-05 Remove locals from dir_next
2022-09-05 Remove locals from dir_rewind
2022-09-05 Move clust2sect param to global
2022-09-05 Move get_fat param to global
2022-09-06 cc65-ify remaining pf functions
2022-09-06 Port check_fs to assembly
2022-09-06 Port clust2sect to assembly
2022-09-06 Inline get_clust
    In FAT16 mode, it's just an assignment operation and only happens once.
2022-09-06 Port _get_fat to assembly
2022-09-06 Optimize mem_cmp
    Pointers need to be on the zero page, cc65 was doing an ugly dance ot make that possible.
2022-09-06 Port mem_cmp to assembly
2022-09-06 Port dir_rewind to assembly
2022-09-06 Port dir_next to assembly
2022-09-07 Port dir_find to assembly
    Now just the top level routines left to go
2022-09-08 Port _pf_open to assembly
2022-09-08 Port pf_mount to assembly
    One method to go!
2022-09-08 Port pf_read and some cleanup
    Assembly port complete! Next step - ROM!
2022-09-08 Add/clarify comments
2022-09-08 Move mmcbpp.s into ROM
2022-09-09 Move PFF code into ROM
2022-09-09 Disk program definition & example chain load
2022-09-25 Fix lib zero page definitions
2022-09-25 Implement disk load in assembly
